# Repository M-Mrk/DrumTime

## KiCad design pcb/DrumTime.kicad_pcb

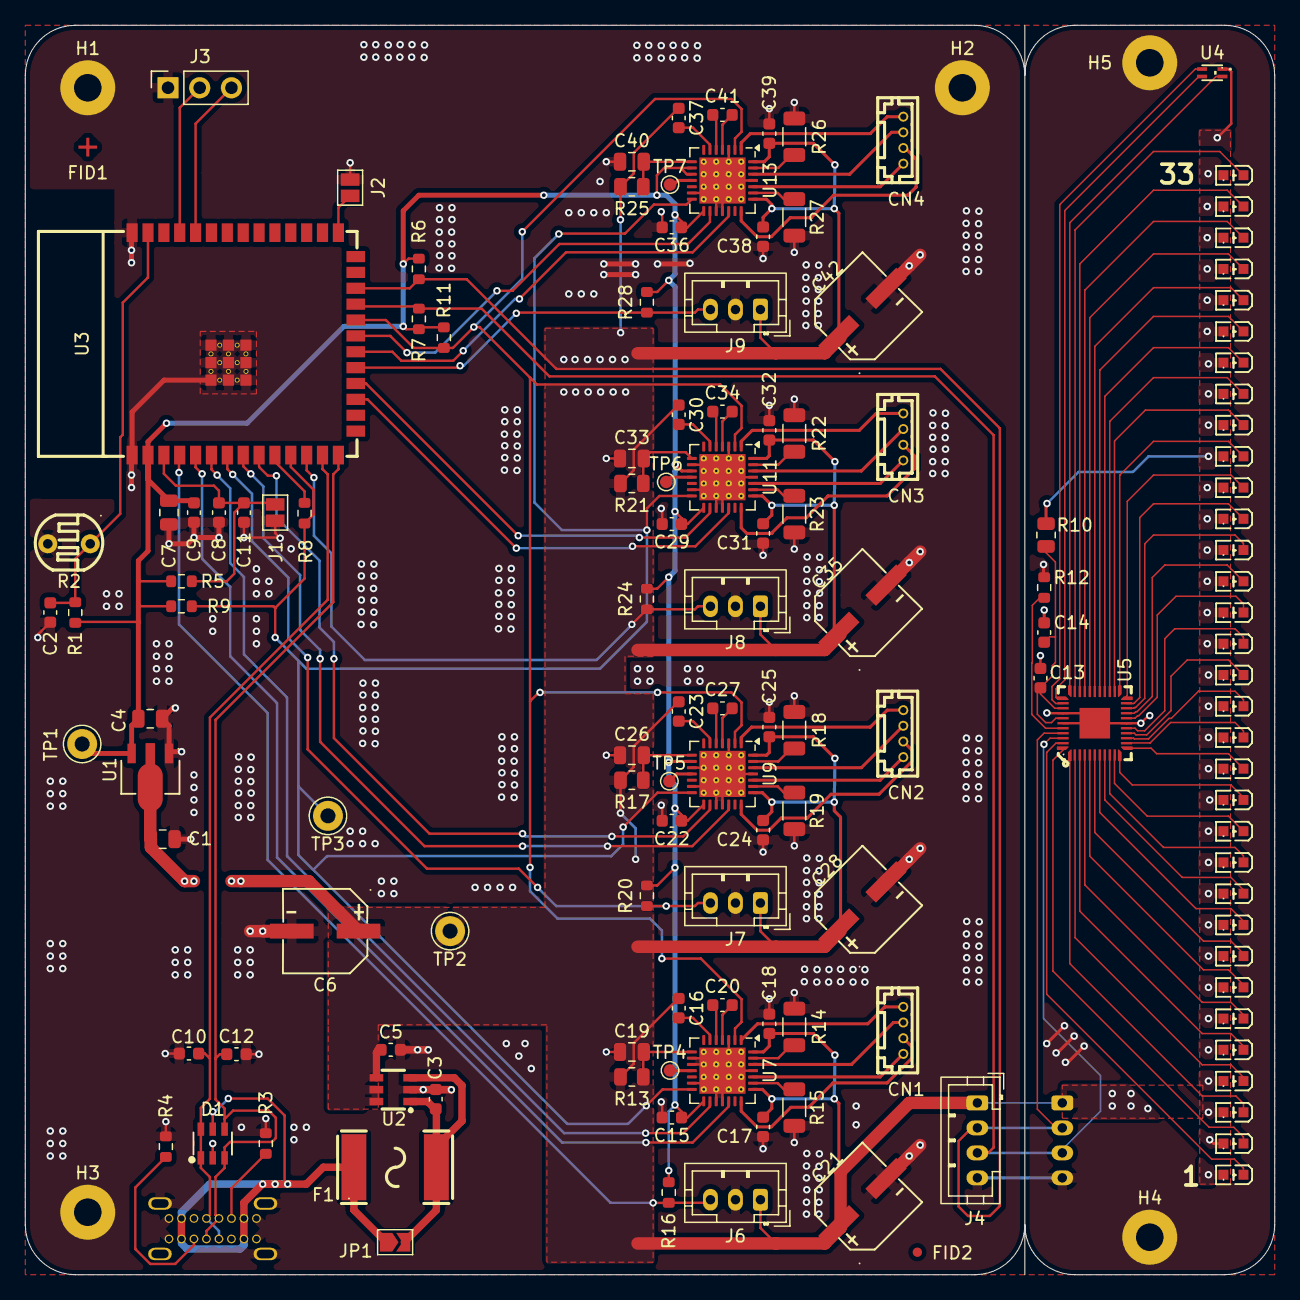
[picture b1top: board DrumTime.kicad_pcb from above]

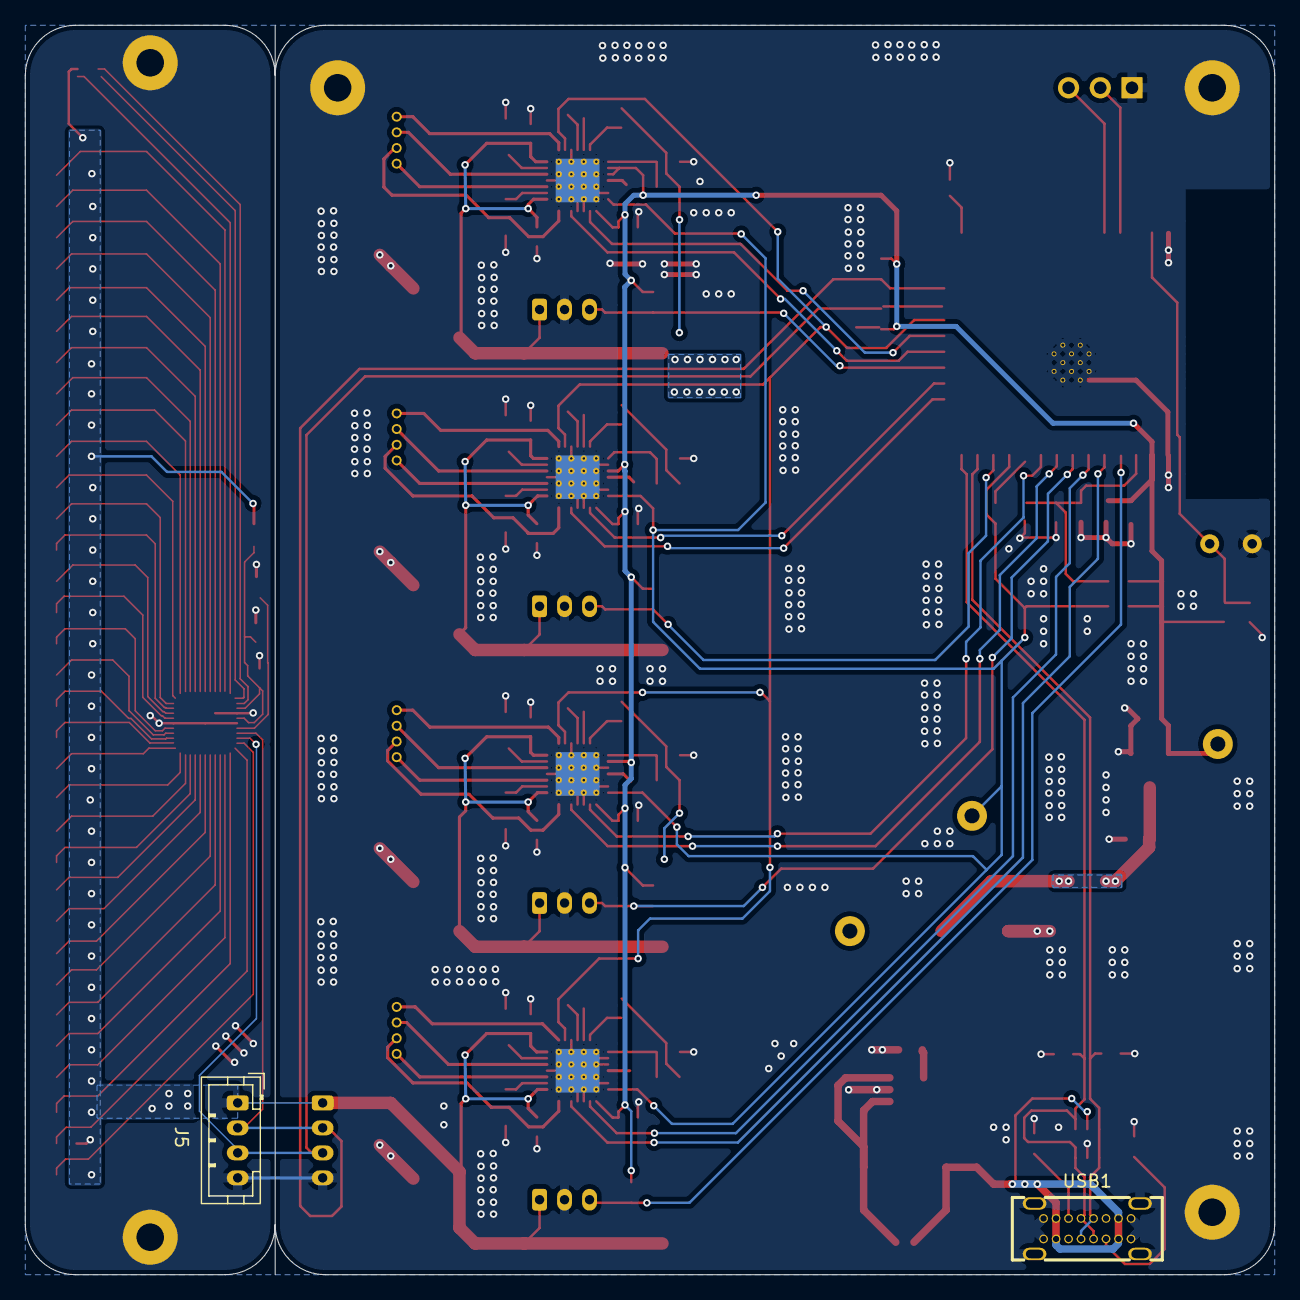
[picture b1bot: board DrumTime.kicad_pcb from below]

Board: 2 copper layers, 100.0 x 100.0 mm, 143 parts (2 on the bottom side), 114 nets.

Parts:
C1, C4, C19, C26, C33, C40: 10uF; C_0805_2012Metric
C2, C8, C9, C13, C15, C16, C17, C18, C22, C23, C24, C25, C29, C30, C31, C32, C36, C37, C38, C39: 100nF; C_0603_1608Metric
C3, C11, C14: 1uF; C_0603_1608Metric
C5, C20, C27, C34, C41: 22nF; C_0603_1608Metric
C6, C21, C28, C35, C42: 100uF; CAP-SMD_BD6.3-L6.6-W6.6-FD
C7: 22uF; C_0805_2012Metric
C10, C12: C; C_0603_1608Metric
CN1, CN2, CN3, CN4: Motor; CONN-TH_530470410
D1: USBLC6-2SC6; SOT-23-6_L2.9-W1.6-P0.95-LS2.8-BL
F1: Polyfuse; F2920
FID1: Fiducial; Fiducial_Cross_1.5mm_Mask2mm
FID2: Fiducial; Fiducial_0.75mm_Mask1.5mm
H1, H2, H3, H4, H5: MountingHole; MountingHole_2.2mm_M2_Pad
J1: EN; SolderJumper-2_P1.3mm_Open_Pad1.0x1.5mm
J2: Boot; SolderJumper-2_P1.3mm_Open_Pad1.0x1.5mm
J3: Debug; PinSocket_1x03_P2.54mm_Vertical
J4, J5: LED_Conn; JST_PH_B4B-PH-K_1x04_P2.00mm_Vertical
J6, J7, J8, J9: Hall; JST_PH_B3B-PH-K_1x03_P2.00mm_Vertical
JP1: JMP Fuse; SolderJumper-2_P1.3mm_Open_TrianglePad1.0x1.5mm
LED1, LED2, LED3, LED4, LED5, LED6, LED7, LED8, LED9, LED10, LED11, LED12, LED13, LED14, LED15, LED16, LED17, LED18, LED19, LED20, LED21, LED22, LED23, LED24, LED25, LED26, LED27, LED28, LED29, LED30, LED31, LED32, LED33: LED0603-R-RD_WHITE
R1, R5, R11, R16, R20, R24, R28: 10kR; R_0603_1608Metric
R2: GL5528; RES-TH_L5.1-W4.3-P3.40-D0.5
R3, R4, R6, R7, R9: 5.1kR; R_0603_1608Metric
R8: 1kR; R_0603_1608Metric
R10, R13, R17, R21, R25: 10R; R_0805_2012Metric
R12: 15kR; R_0603_1608Metric
R14, R15, R18, R19, R22, R23, R26, R27: 0.33R; R_1206_3216Metric
TP1: 3V3; Pin_D1.0mm_L10.0mm_LooseFit
TP2: 5V; Pin_D1.0mm_L10.0mm_LooseFit
TP3: UART; Pin_D1.0mm_L10.0mm_LooseFit
TP4, TP5, TP6, TP7: Diag; TestPoint_Pad_D1.0mm
U1: ME6210A33PG; SOT-89_L4.5-W2.5-P1.50-LS4.2-BR
U2: TPS22918TDBVRQ1; SOT-23-6_L2.9-W1.6-P0.95-LS2.8-BR
U3: ESP32-S3-WROOM-1-N8; WIFIM-SMD_ESP32-S3-WROOM-1-N8
U4: TJ-S1608SW6TDSLCCYRGB-A5; LED-ARRAY-SMD_4P-L1.6-W0.8-BL-FD
U5: IS31FL3236A-QFLS2-TR; QFN-44_L5.0-W5.0-P0.40-BL-EP
U7, U9, U11, U13: TMC2209-LA; VQFN-28-1EP_5x5mm_P0.5mm_EP3.7x3.7mm_ThermalVias
USB1: Type-C; USB-C-TH_TYPE-C16PLCH10.0-B143

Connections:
+3V3: C4.1, C7.1, C9.1, C15.1, C22.1, C29.1, C36.1, R1.2, R5.1, R6.1, R7.1, R9.1, R11.1, R16.1, R20.1, R24.1, R28.1, TP1.1 (1_1), U1.3 (Vout), U3.2 (3V3), U7.15 (VCC_IO), U9.9 (MS1/AD0), U9.15 (VCC_IO), U11.10 (MS2/AD1), U11.15 (VCC_IO), U13.9 (MS1/AD0), U13.10 (MS2/AD1), U13.15 (VCC_IO)
+5V: C1.1, C6.1, C16.1, C17.1, C18.1, C21.1, C23.1, C24.1, C25.1, C28.1, C30.1, C31.1, C32.1, C35.1, C37.1, C38.1, C39.1, C42.1, J4.1, J5.1, J6.1, J7.1, J8.1, J9.1, LED1.1 (A), LED2.1 (A), LED3.1 (A), LED4.1 (A), LED5.1 (A), LED6.1 (A), LED7.1 (A), LED8.1 (A), LED9.1 (A), LED10.1 (A), LED11.1 (A), LED12.1 (A), LED13.1 (A), LED14.1 (A), LED15.1 (A), LED16.1 (A), LED17.1 (A), LED18.1 (A), LED19.1 (A), LED20.1 (A), LED21.1 (A), LED22.1 (A), LED23.1 (A), LED24.1 (A), LED25.1 (A), LED26.1 (A), LED27.1 (A), LED28.1 (A), LED29.1 (A), LED30.1 (A), LED31.1 (A), LED32.1 (A), LED33.1 (A), R10.1, R13.1, R17.1, R21.1, R25.1, TP2.1 (1_1), U1.2 (Vin), U2.5 (QOD), U2.6 (VOUT), U4.1 (+), U7.22 (VS), U7.28 (VS), U9.22 (VS), U9.28 (VS), U11.22 (VS), U11.28 (VS), U13.22 (VS), U13.28 (VS)
/LDR_sense: C2.1, R1.1, R2.1, U3.39 (IO1)
/LEDs/1: LED1.2 (K), U5.43 (OUT1)
/LEDs/2: LED2.2 (K), U5.44 (OUT2)
/LEDs/3: LED3.2 (K), U5.1 (OUT3)
/LEDs/4: LED4.2 (K), U5.2 (OUT4)
/LEDs/5: LED5.2 (K), U5.3 (OUT5)
/LEDs/6: LED6.2 (K), U5.4 (OUT6)
/LEDs/7: LED7.2 (K), U5.5 (OUT7)
/LEDs/8: LED8.2 (K), U5.6 (OUT8)
/LEDs/9: LED9.2 (K), U5.7 (OUT9)
/LEDs/10: LED10.2 (K), U5.8 (OUT10)
/LEDs/11: LED11.2 (K), U5.9 (OUT11)
/LEDs/12: LED12.2 (K), U5.10 (OUT12)
/LEDs/13: LED13.2 (K), U5.11 (OUT13)
/LEDs/14: LED14.2 (K), U5.12 (OUT14)
/LEDs/15: LED15.2 (K), U5.13 (OUT15)
/LEDs/16: LED16.2 (K), U5.14 (OUT16)
/LEDs/17: LED17.2 (K), U5.15 (OUT17)
/LEDs/18: LED18.2 (K), U5.16 (OUT18)
/LEDs/19: LED19.2 (K), U5.18 (OUT19)
/LEDs/20: LED20.2 (K), U5.19 (OUT20)
/LEDs/21: LED21.2 (K), U5.20 (OUT21)
/LEDs/22: LED22.2 (K), U5.21 (OUT22)
/LEDs/23: LED23.2 (K), U5.22 (OUT23)
/LEDs/24: LED24.2 (K), U5.23 (OUT24)
/LEDs/25: LED25.2 (K), U5.24 (OUT25)
/LEDs/26: LED26.2 (K), U5.25 (OUT26)
/LEDs/27: LED27.2 (K), U5.26 (OUT27)
/LEDs/28: LED28.2 (K), U5.27 (OUT28)
/LEDs/29: LED29.2 (K), U5.28 (OUT29)
/LEDs/30: LED30.2 (K), U5.29 (OUT30)
/LEDs/31: LED31.2 (K), U5.30 (OUT31)
/LEDs/32: LED32.2 (K), U5.31 (OUT32)
/LEDs/33: LED33.2 (K), U5.32 (OUT33)
/Motor1/A+: CN2.1, U9.24 (OA1)
/Motor1/A-: CN2.2, U9.21 (OA2)
/Motor1/B+: CN2.3, U9.26 (OB1)
/Motor1/B-: CN2.4, U9.1 (OB2)
/Motor2/A+: CN3.1, U11.24 (OA1)
/Motor2/A-: CN3.2, U11.21 (OA2)
/Motor2/B+: CN3.3, U11.26 (OB1)
/Motor2/B-: CN3.4, U11.1 (OB2)
/Motor3/A+: CN4.1, U13.24 (OA1)
/Motor3/A-: CN4.2, U13.21 (OA2)
/Motor3/B+: CN4.3, U13.26 (OB1)
/Motor3/B-: CN4.4, U13.1 (OB2)
/Motor/A+: CN1.1, U7.24 (OA1)
/Motor/A-: CN1.2, U7.21 (OA2)
/Motor/B+: CN1.3, U7.26 (OB1)
/Motor/B-: CN1.4, U7.1 (OB2)
/RGB_B: U4.2 (-), U5.35 (OUT36)
/RGB_G: U4.3 (-), U5.34 (OUT35)
/RGB_R: U4.4 (-), U5.33 (OUT34)
/SCL: J4.3, J5.3, R7.2, U3.23 (IO21), U5.42 (SCL)
/SDA: J4.2, J5.2, R6.2, U3.24 (IO47), U5.41 (SDA)
/SDB: C13.1, C14.1, R10.2, U5.36 (SDB), U5.38 (VCC)
/USB_D+: C12.1, D1.3, D1.4, U3.14 (IO20), USB1.A6 (DP1), USB1.B6 (DP2)
/USB_D-: C10.1, D1.1, D1.6, U3.13 (IO19), USB1.A7 (DN1), USB1.B7 (DN2)
/cc1: R3.1, USB1.A5 (CC1)
/cc2: R4.1, USB1.B5 (CC2)
/m0_dir: U3.5 (IO5), U7.19 (DIR)
/m0_hall: J6.3, R16.2, U3.4 (IO4)
/m0_step: U3.6 (IO6), U7.16 (STEP)
/m1_dir: U3.8 (IO15), U9.19 (DIR)
/m1_hall: J7.3, R20.2, U3.7 (IO7)
/m1_step: U3.9 (IO16), U9.16 (STEP)
/m2_dir: U3.17 (IO9), U11.19 (DIR)
/m2_hall: J8.3, R24.2, U3.12 (IO8)
/m2_step: U3.18 (IO10), U11.16 (STEP)
/m3_dir: U3.20 (IO12), U13.19 (DIR)
/m3_hall: J9.3, R28.2, U3.19 (IO11)
/m3_step: U3.21 (IO13), U13.16 (STEP)
/m_enn: R11.2, U3.22 (IO14), U7.2 (~EN), U9.2 (~EN), U11.2 (~EN), U13.2 (~EN)
/m_uart: R8.2, R9.2, TP3.1 (1_1), U3.11 (IO18), U7.14 (~PD/UART), U9.14 (~PD/UART), U11.14 (~PD/UART), U13.14 (~PD/UART)
/uart1_tx: R8.1, U3.10 (IO17)
GND: C1.2, C2.2, C3.2, C4.2, C5.2, C6.2, C7.2, C8.2, C9.2, C10.2, C11.2, C12.2, C13.2, C14.2, C15.2, C17.2, C18.2, C19.1, C21.2, C22.2, C24.2, C25.2, C26.1, C28.2, C29.2, C31.2, C32.2, C33.1, C35.2, C36.2, C38.2, C39.2, C40.1, C42.2, D1.2, H1.1 (1_1), H2.1 (1_1), H3.1 (1_1), H4.1 (1_1), H5.1 (1_1), J1.2, J2.2, J3.1, J4.4, J5.4, J6.2, J7.2, J8.2, J9.2, R2.2, R3.2, R4.2, R12.2, R14.2, R15.2, R18.2, R19.2, R22.2, R23.2, R26.2, R27.2, U1.1 (Vss), U2.2 (GND), U3.1 (GND), U3.40 (GND), U3.41 (EP), U5.17 (GND), U5.37 (AD), U5.39 (GND), U5.45 (EPAD), U7.3 (GND), U7.9 (MS1/AD0), U7.10 (MS2/AD1), U7.13 (CLK), U7.17 (VREF), U7.18 (GND), U7.25 (NC), U7.29 (GND), U9.3 (GND), U9.10 (MS2/AD1), U9.13 (CLK), U9.17 (VREF), U9.18 (GND), U9.25 (NC), U9.29 (GND), U11.3 (GND), U11.9 (MS1/AD0), U11.13 (CLK), U11.17 (VREF), U11.18 (GND), U11.25 (NC), U11.29 (GND), U13.3 (GND), U13.13 (CLK), U13.17 (VREF), U13.18 (GND), U13.25 (NC), U13.29 (GND), USB1.0 (EH), USB1.A1 (GND), USB1.A12 (GND), USB1.B1 (GND), USB1.B12 (GND)
unnamed: C8.1, C11.1, J1.1, R5.2, U3.3 (EN)
unnamed: J2.1, U3.27 (IO0)
unnamed: J3.2, U3.37 (TXD0)
unnamed: J3.3, U3.36 (RXD0)
unnamed: C3.1, F1.2, JP1.2 (B), U2.1 (VIN), U2.3 (ON)
unnamed: C5.1, U2.4 (CT)
unnamed: R12.1, U5.40 (R-EXT)
unnamed: C19.2, R13.2, U7.8 (5VOUT)
unnamed: R15.1, U7.23 (BRA)
unnamed: R14.1, U7.27 (BRB)
unnamed: C20.2, U7.5 (CPI)
unnamed: C20.1, U7.4 (CPO)
unnamed: TP4.1 (1_1), U7.11 (DIAG)
unnamed: C16.2, U7.6 (VCP)
unnamed: C26.2, R17.2, U9.8 (5VOUT)
unnamed: R19.1, U9.23 (BRA)
unnamed: R18.1, U9.27 (BRB)
unnamed: C27.2, U9.5 (CPI)
unnamed: C27.1, U9.4 (CPO)
unnamed: TP5.1 (1_1), U9.11 (DIAG)
unnamed: C23.2, U9.6 (VCP)
unnamed: C33.2, R21.2, U11.8 (5VOUT)
unnamed: R23.1, U11.23 (BRA)
unnamed: R22.1, U11.27 (BRB)
unnamed: C34.2, U11.5 (CPI)
unnamed: C34.1, U11.4 (CPO)
unnamed: TP6.1 (1_1), U11.11 (DIAG)
unnamed: C30.2, U11.6 (VCP)
unnamed: C40.2, R25.2, U13.8 (5VOUT)
unnamed: R27.1, U13.23 (BRA)
unnamed: R26.1, U13.27 (BRB)
unnamed: C41.2, U13.5 (CPI)
unnamed: C41.1, U13.4 (CPO)
unnamed: TP7.1 (1_1), U13.11 (DIAG)
unnamed: C37.2, U13.6 (VCP)
VBUS: D1.5, F1.1, JP1.1 (A), USB1.A4 (VBUS), USB1.A9 (VBUS), USB1.B4 (VBUS), USB1.B9 (VBUS)
